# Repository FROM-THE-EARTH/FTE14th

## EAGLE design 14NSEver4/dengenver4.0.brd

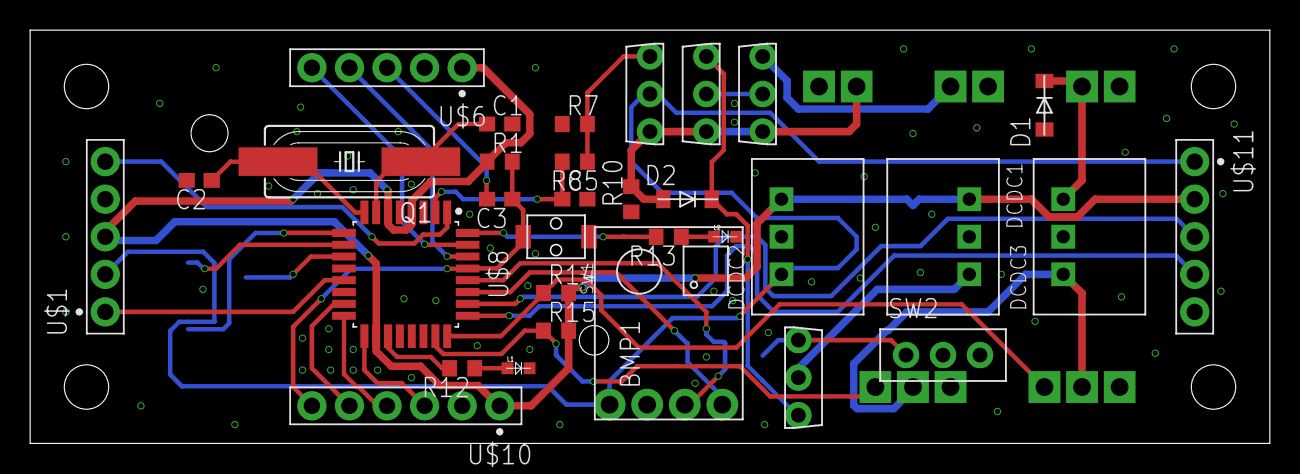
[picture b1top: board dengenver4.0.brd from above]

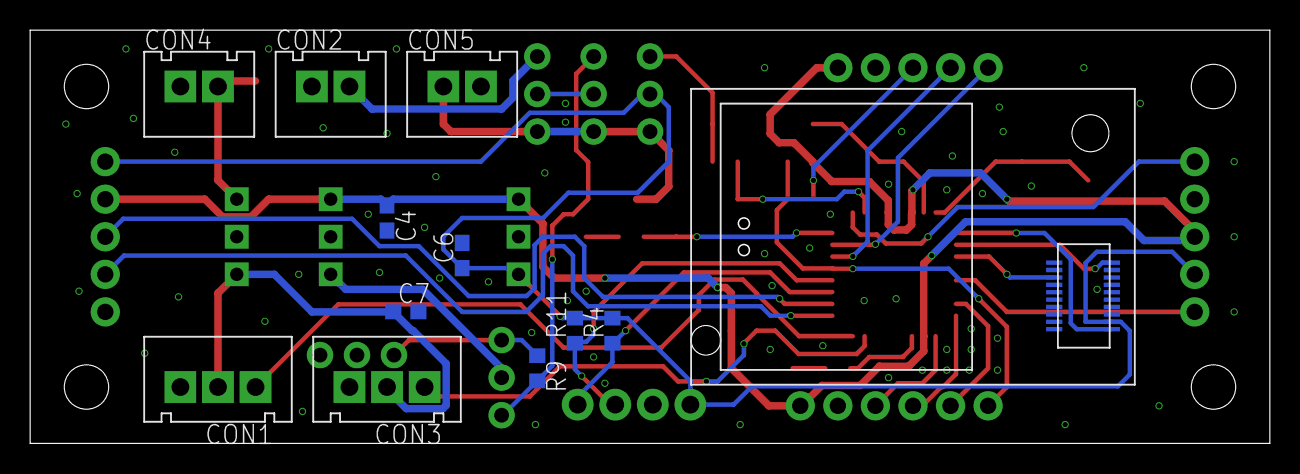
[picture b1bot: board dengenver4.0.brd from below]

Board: 2 copper layers, 83.8 x 27.9 mm, 44 parts (12 on the bottom side), 37 nets.

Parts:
BMP1: BMP180; GY-68
C1, C2: 22p; C1608
C3: 0.1μ; C1608
C4, C6: 3.3uF; C1608
C5: 10uF; C1608
C7: 3.3uF; C0603
CON1, CON3: 3PIN
CON2, CON4, CON5: 2PIN
D1, D2: SOD-123
DCDC1, DCDC3: 5V1A_M78AR05-1
DCDC2: 3.3V1A_M78AR033-1
IM2: IM920_IM920C
L1, L2: OSXX1608C1A
Q1: 16mhz; HC49UP
R1, R4, R7, R11: 10k; R0603
R8, R10: 1k; R0603
R9: 100k; R0603
R12, R13: 100; R0603
R14, R15: 4.7k; R0603
SW1: TVAF06-A020B-R
SW2: SRIDE_SWITCH
U$1, U$6, U$11: 1X5; HDRVR5W64P254_1X5_1310X250X865B
U$2, U$4, U$5: 2SJ681-PCH; 2SJ681
U$3: 2SK4017-NCH; 2SK4017
U$8: ATMEGA328P-AU; QFP80P900X900X120-32N
U$10: 1X61X6_2.5; HDRVR6W64P254_1X6_1564X250X865B

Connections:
+3V3: BMP1.P1, C6.1, DCDC2.VOUT, IM2.$P17, R4.2, R11.2, U$1.2, U$3.DRAIN, U$11.1
+5V: C4.1, DCDC1.VOUT, DCDC2.VIN, R1.1, R14.2, R15.2, U$1.3, U$6.1, U$8.AVCC, U$8.VCC1, U$8.VCC2, U$10.1, U$11.2
+5V1: DCDC1.VIN, U$5.DRAIN
BORD1: U$1.5, U$8.PD3
BORD2: U$1.1, U$8.PB1
BORDRX: U$8.PC3, U$11.3
BORDTX: U$8.PC2, U$11.4
FP: CON5.P$1, D2.C, R10.2, U$2.GATE, U$3.GATE, U$4.GATE
FP_CHECKER: C5.1, R8.2, U$8.PD4
GND: BMP1.P2, C1.2, C2.2, C4.2, C5.2, C6.2, C7.2, CON1.P$3, CON2.P$1, CON3.P$3, CON4.P$1, CON5.P$2, DCDC1.GND, DCDC2.GND, DCDC3.GND, IM2.$P18, L1.CT, L2.CT, R7.1, R10.1, SW1.P$1, SW2.LR, U$1.4, U$6.2, U$8.GND1, U$8.GND2, U$8.GND3, U$10.2, U$11.5
IM_BUSY: IM2.$P1, U$8.PD6
IM_RESET: IM2.$P19, U$8.PD5
LED_1.0: R13.2, U$8.PD2
LED_1.1: R12.2, U$8.ADC6
MISO: U$8.PB4, U$10.4
MOSI: U$8.PB3, U$10.5
unnamed: U$2.DRAIN, U$4.DRAIN
unnamed: D2.A, R9.2, U$4.SOURCE, U$5.SOURCE
unnamed: L2.AN, R13.1
unnamed: L1.AN, R12.1
unnamed: C1.1, Q1.1, U$8.PB6
unnamed: C2.1, Q1.2, U$8.PB7
unnamed: R7.2, R8.1, U$3.SOURCE
RAW: CON2.P$2, U$2.SOURCE
RESET: C3.2, U$6.3
RESETB: C3.1, R1.2, SW1.P$2, U$8.PC6, U$10.6
RX: U$6.4, U$8.PD0
RX_IM: IM2.$P6, U$8.PD7
SCK: U$8.PB5, U$10.3
SCL: BMP1.P3, R11.1, U$8.PC5
SDA: BMP1.P4, R4.1, U$8.PC4
SERVO1: CON1.P$1, R14.1, U$8.PC1
SERVO2: CON3.P$1, R15.1, U$8.PC0
SERVO5V: C7.1, CON1.P$2, CON3.P$2, DCDC3.VOUT
SERVORAW: CON4.P$2, D1.A, DCDC3.VIN
SW: R9.1, SW2.L, U$5.GATE
TX: U$6.5, U$8.PD1

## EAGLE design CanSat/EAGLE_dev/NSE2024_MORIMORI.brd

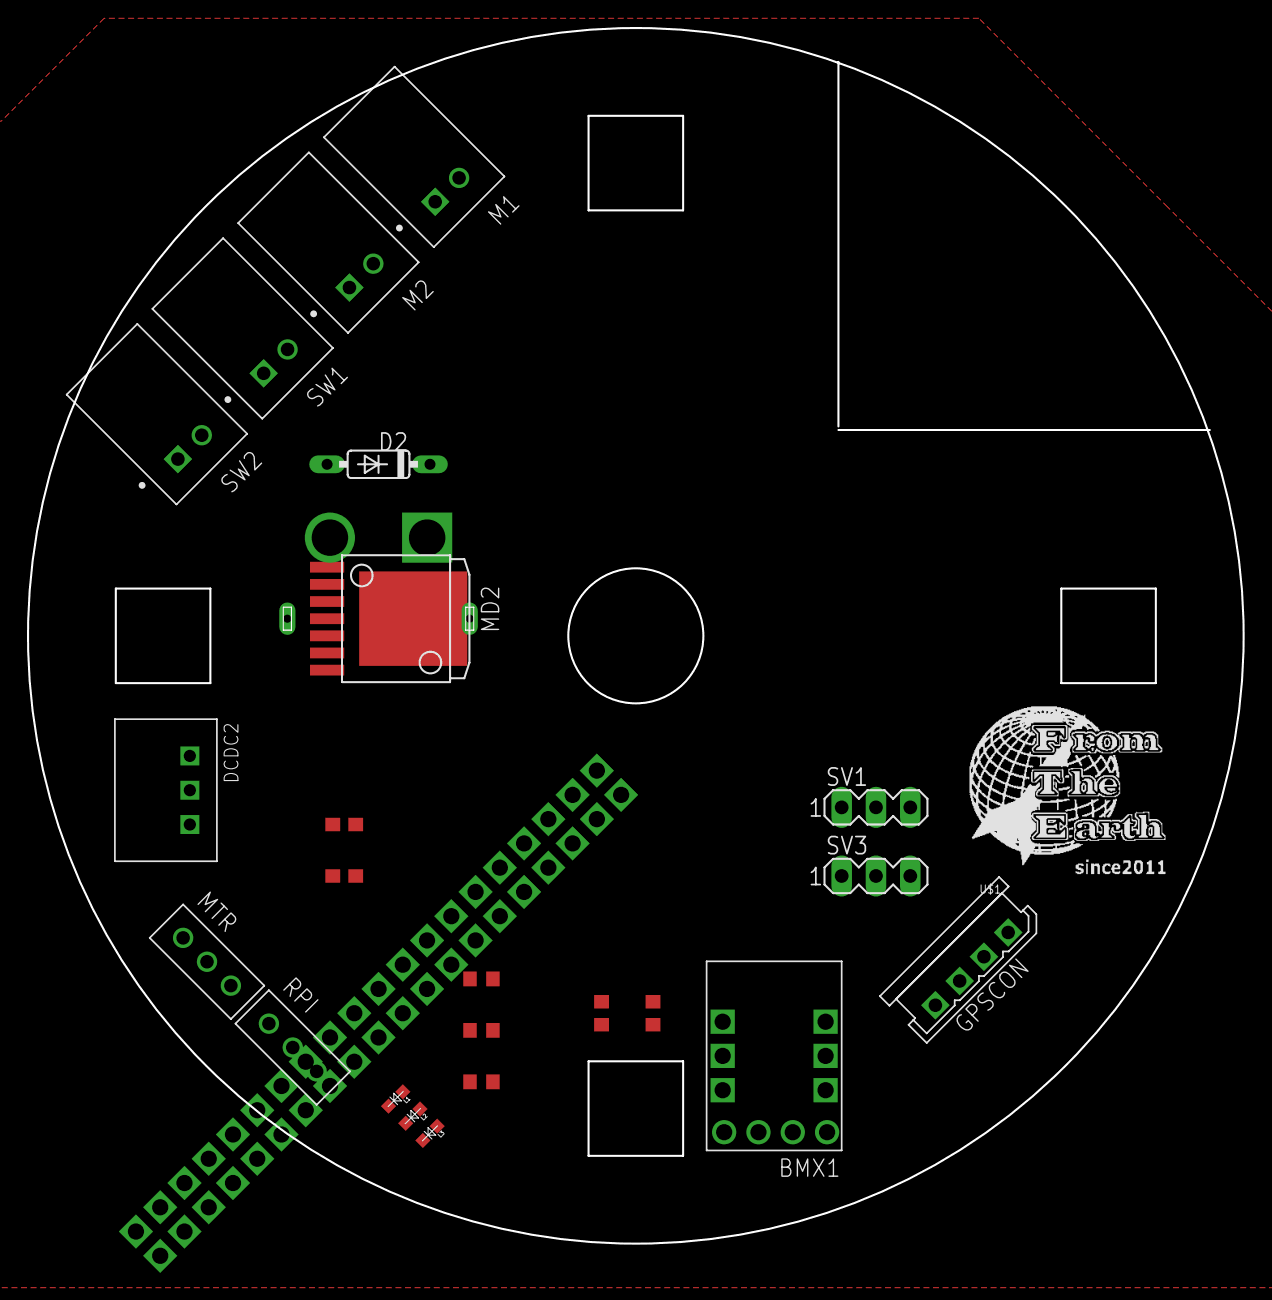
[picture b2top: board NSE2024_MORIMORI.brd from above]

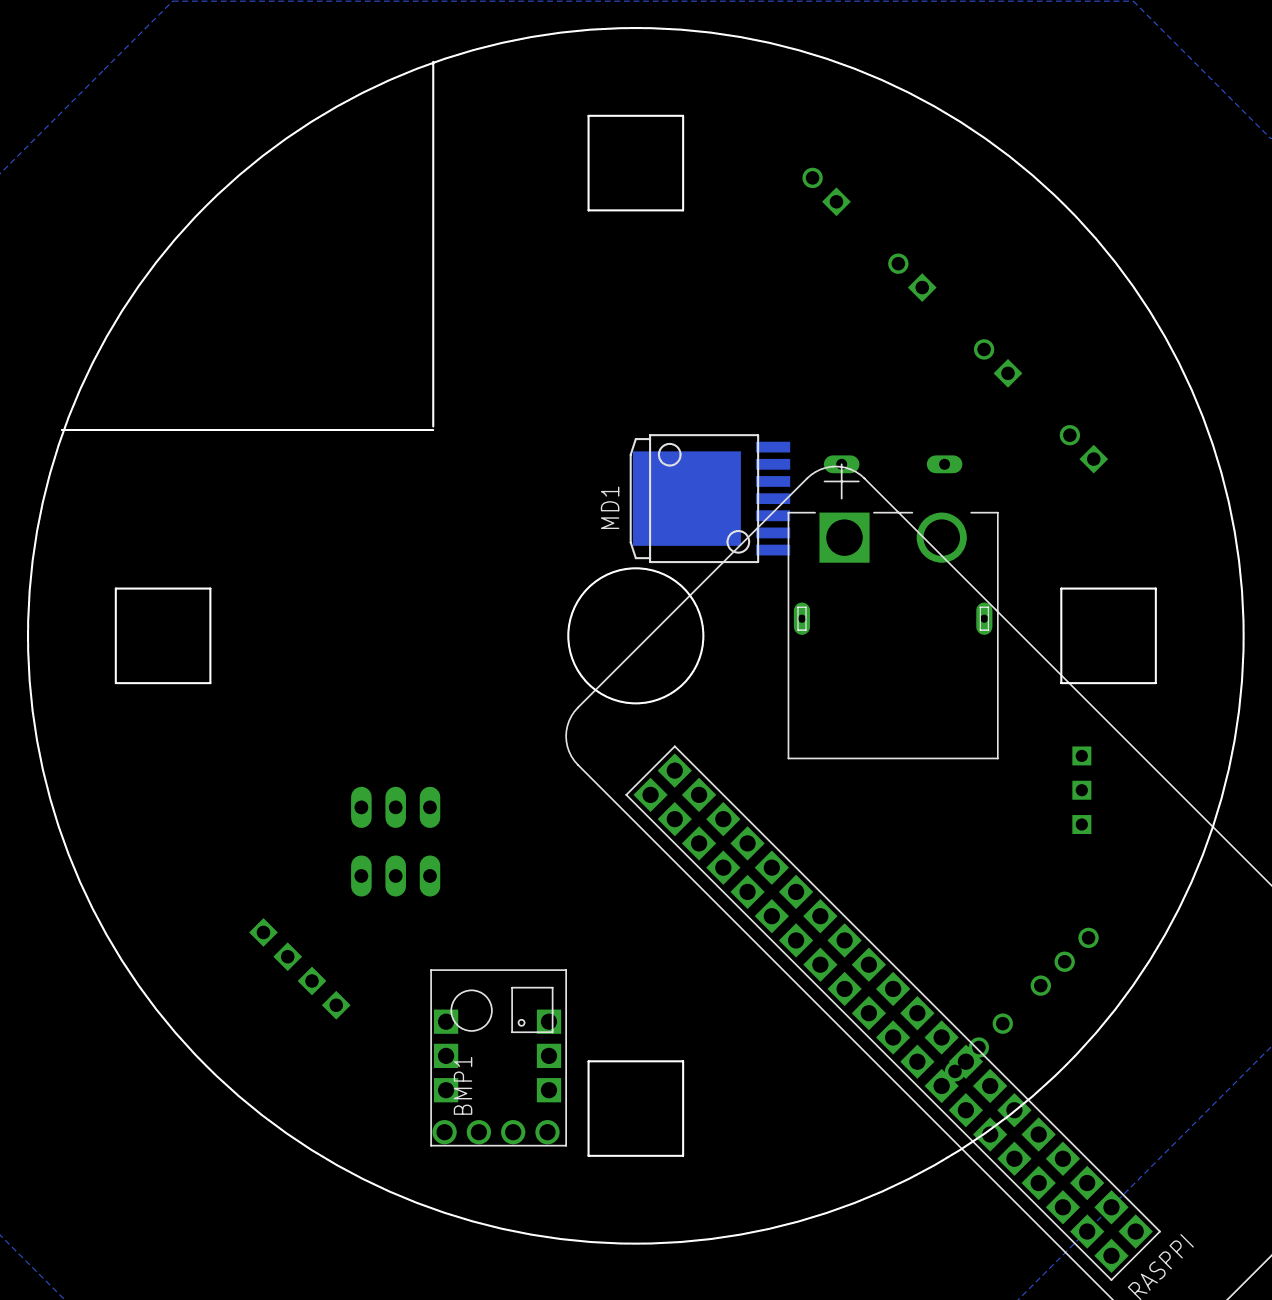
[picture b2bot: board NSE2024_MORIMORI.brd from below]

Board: 2 copper layers, 90.0 x 90.0 mm, 28 parts (4 on the bottom side), 27 nets, no tracks yet.

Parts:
BMP1: BMP180; GY-68
BMX1: BMX055
C1, C3: 10μF; C0603
D2: 1N4148DO35-7; DO35-7
DCDC2: 3.3V1A_M78AR033-1
GPSCON: 2.5_MINI-SPOX_4PIN
L1, L2, L3: OSXX1608C1A
M1, M2: S2B-XH-A(LF)(SN); JST_S2B-XH-A(LF)(SN)
MD1, MD2: BD6222HFP-TR
MTR: SRIDE_SWITCH
POWER: XT60PW-M; AMASS_XT60PW-M
R4, R6: 1k; R0603
R7, R12, R14: 100; R0603
RASPPI: RASPBERYPIZEROW
RPI: SRIDE_SWITCH
SV1, SV3: MA03-1
SW1, SW2: S2B-XH-A(LF)(SN); JST_S2B-XH-A(LF)(SN)
U$1: F.T.E.LOGO; LOGO

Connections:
+3V3: BMP1.P1, BMX1.3V3, BMX1.VCC, BMX1.VCCIO, R4.1, R6.1, RASPPI.3.3V1, RASPPI.3.3V2
+5V: C1.1, DCDC2.VOUT, GPSCON.P$4, RASPPI.5V1, RASPPI.5V2, RPI.L, SV1.2, SV3.2
+12V: C3.1, D2.C, DCDC2.VIN, MD1.VCC, MD1.VREV, MD2.VCC, MD2.VREV, MTR.L
GND: BMP1.P2, BMX1.GND, C1.2, C3.2, DCDC2.GND, GPSCON.P$1, L1.CT, L2.CT, L3.CT, MD1.BGND, MD1.GND, MD2.BGND, MD2.GND, POWER.1, RASPPI.GND1, RASPPI.GND2, RASPPI.GND3, RASPPI.GND4, RASPPI.GND5, RASPPI.GND6, RASPPI.GND7, RASPPI.GND8, SV1.1, SV3.1, SW1.2, SW2.1
GPS_RX: GPSCON.P$2, RASPPI.GPIO15
GPS_TX: GPSCON.P$3, RASPPI.GPIO14
LED0: R12.1, RASPPI.GPIO25
LED1: R7.1, RASPPI.GPIO8
LED2: R14.1, RASPPI.GPIO7
MD1_F: MD1.FIN, RASPPI.GPIO5
MD1_O1: M1.1, MD1.OUT1
MD1_O2: M1.2, MD1.OUT2
MD1_R: MD1.RIN, RASPPI.GPIO6
MD2_F: MD2.FIN, RASPPI.GPIO13
MD2_O1: M2.2, MD2.OUT1
MD2_O2: M2.1, MD2.OUT2
MD2_R: MD2.RIN, RASPPI.GPIO19
unnamed: D2.A, POWER.2
unnamed: L1.AN, R12.2
unnamed: L2.AN, R7.2
unnamed: L3.AN, R14.2
PWM: RASPPI.GPIO10, SV3.3
PWM1: RASPPI.GPIO9, SV1.3
SCL: BMP1.P3, BMX1.SCL, R4.2, RASPPI.GPIO3
SDA: BMP1.P4, BMX1.SDA, R6.2, RASPPI.GPIO2
SW1: RASPPI.GPIO16, SW1.1
SW2: RASPPI.GPIO20, SW2.2

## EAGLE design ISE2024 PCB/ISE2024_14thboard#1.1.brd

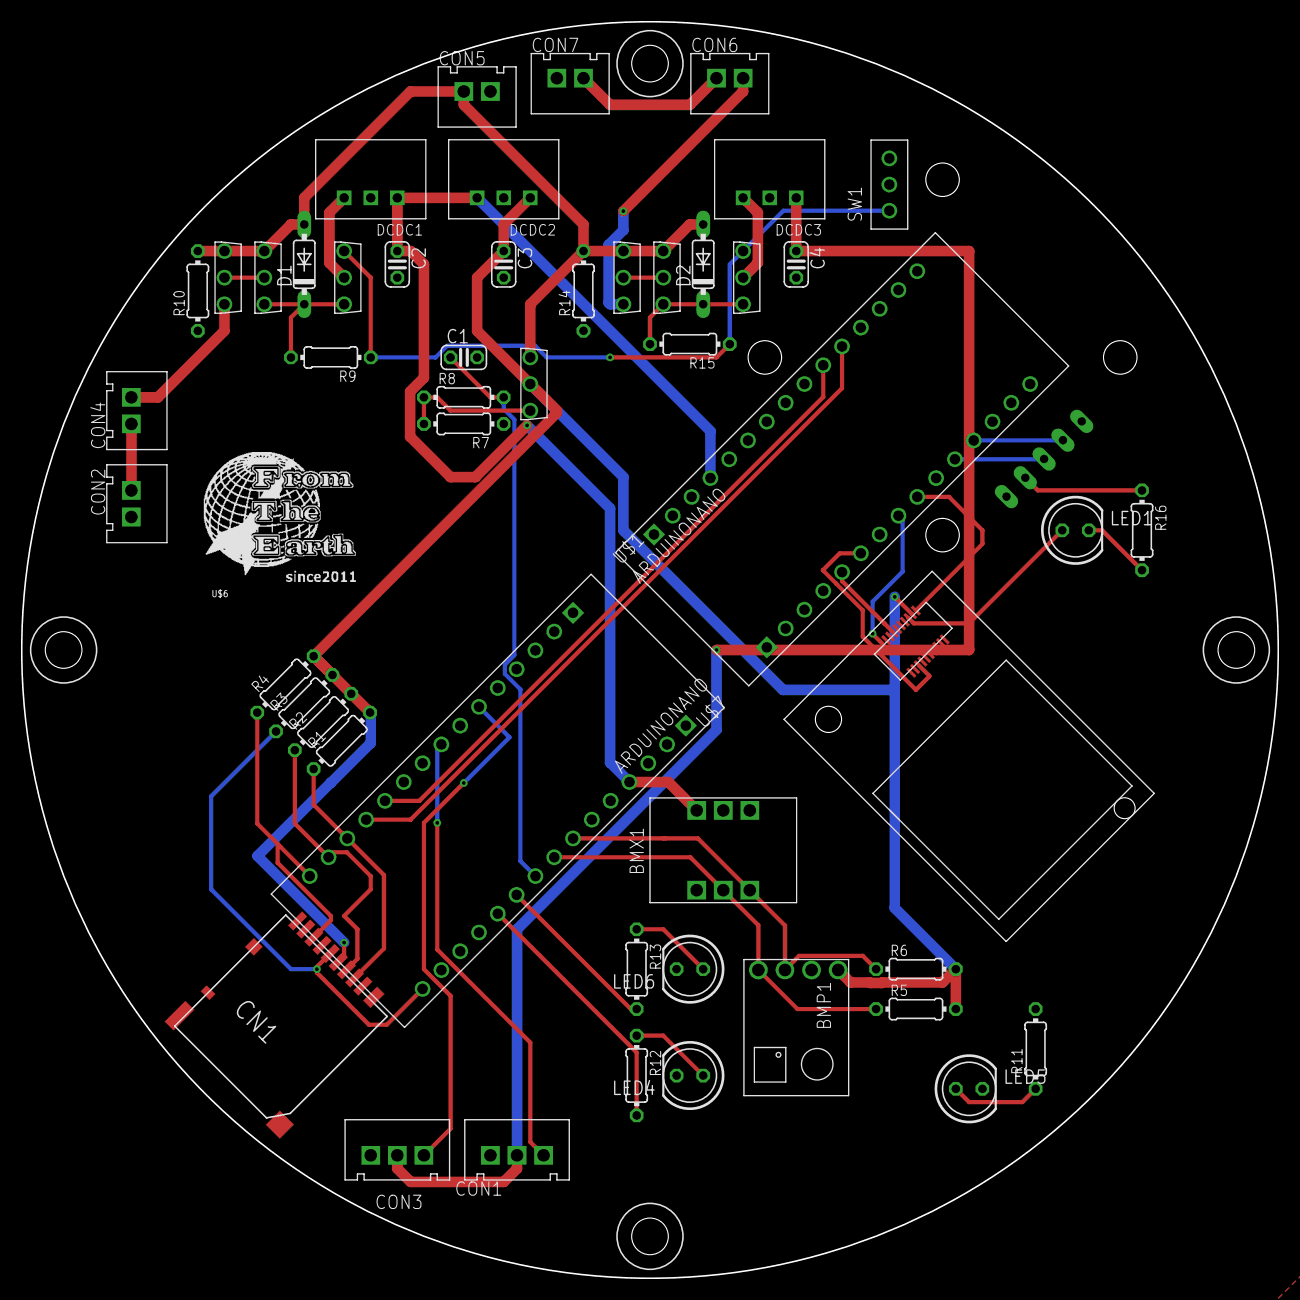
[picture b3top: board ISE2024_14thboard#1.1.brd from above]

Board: 2 copper layers, 120.0 x 120.0 mm, 52 parts (1 on the bottom side), 41 nets.

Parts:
BMP1: BMP180; GY-68
BMX1: BMX055
C1: 10uF; C025-024X044
C2, C3, C4: 3.3uF; C025-024X044
CN1: DM3AT
CON1, CON3: 3PIN
CON2, CON4, CON5, CON6, CON7: 2PIN
D1, D2: 1N4148DO35-7; DO35-7
DCDC1, DCDC3: 5V1A_M78AR05-1
DCDC2: 3.3V1A_M78AR033-1
IM2: IM920_IM920C
LED1, LED4, LED5, LED6: LED5MM
R1, R2, R3, R4, R5, R6, R7: 10k; 0204/7
R8, R10, R14: 1k; 0204/7
R9, R15: 100k; 0204/7
R11, R12, R13, R16: 100; 0204/7
SW1: SRIDE_SWITCH
U$1, U$7: ARDUINONANO
U$2, U$4, U$5, U$8, U$9, U$10: 2SJ681-PCH; 2SJ681
U$3: 2SK4017-NCH; 2SK4017
U$6: F.T.E.LOGO; LOGO
U$11: AE-GYSFDMAXB

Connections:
3.3_RAW1: CON4.P$2, U$2.SOURCE
3.3_RAW2: CON2.P$2, CON4.P$1
3.3_SV1: CON6.P$2, U$8.SOURCE
3.3_SV2: CON6.P$1, CON7.P$2
+3V3: BMP1.P1, C3.1, CN1.VDD, DCDC2.VOUT, IM2.$P17, R1.2, R2.2, R3.2, R4.2, R5.2, R6.2, U$3.DRAIN
+5V: BMX1.VCC, C2.1, DCDC1.VOUT, DCDC2.VIN, U$1.5V, U$7.5V
+5V1: DCDC1.VIN, U$5.DRAIN
+5V2: DCDC3.VIN, U$9.DRAIN
+5V_SV: C4.1, CON1.P$2, CON3.P$2, DCDC3.VOUT
BOARD-RX: U$1.D8, U$7.D16
BOARD-TX: U$1.D9, U$7.D15
CLK: CN1.CLK, R3.1, U$1.D13
FP: CON5.P$1, D1.A, D2.A, R10.2, R14.2, U$2.GATE, U$3.GATE, U$4.GATE, U$8.GATE, U$10.GATE
FP_CHECKER: C1.1, R8.2, U$1.D17
GND: BMP1.P2, BMX1.GND, C1.2, C2.2, C3.2, C4.2, CN1.VSS, CON1.P$3, CON2.P$1, CON3.P$3, CON5.P$2, CON7.P$1, DCDC1.GND, DCDC2.GND, DCDC3.GND, IM2.$P18, LED4.K, LED5.K, LED6.K, R7.1, R10.1, R14.1, R16.1, SW1.LR, U$1.GND1, U$1.GND2, U$7.GND1, U$11.P2
IM_BUSY: IM2.$P1, U$7.D5
IM_RESET: IM2.$P19, U$7.D6
LED: IM2.$P15, LED1.A
LED1.0: R13.2, U$1.D16
LED1.1: R12.2, U$1.D15
unnamed: U$2.DRAIN, U$4.DRAIN
unnamed: LED6.A, R13.1
unnamed: D1.C, R9.2, U$4.SOURCE, U$5.SOURCE
unnamed: D2.C, R15.2, U$9.SOURCE, U$10.SOURCE
unnamed: U$8.DRAIN, U$10.DRAIN
unnamed: LED4.A, R12.1
unnamed: LED1.K, R16.2
unnamed: LED5.A, R11.1
unnamed: R7.2, R8.1, U$3.SOURCE
RX_GPS: U$7.D9, U$11.P4
RX_IM: IM2.$P6, U$7.D3
SCL: BMP1.P3, BMX1.SCL, R6.1, U$1.D19
SD-MISO: CN1.DAT0, R4.1, U$1.D12
SD-MOSI: CN1.CMD, R2.1, U$1.D11
SD-SS: CN1.CD/DAT3, R1.1, U$1.D10
SDA: BMP1.P4, BMX1.SDA, R5.1, U$1.D18
SERVO1: CON1.P$1, U$1.D5
SERVO2: CON3.P$1, U$1.D3
SW: R9.1, R15.1, SW1.L, U$5.GATE, U$9.GATE
TX_GPS: U$7.D8, U$11.P3
TX_IM: IM2.$P7, U$7.D2

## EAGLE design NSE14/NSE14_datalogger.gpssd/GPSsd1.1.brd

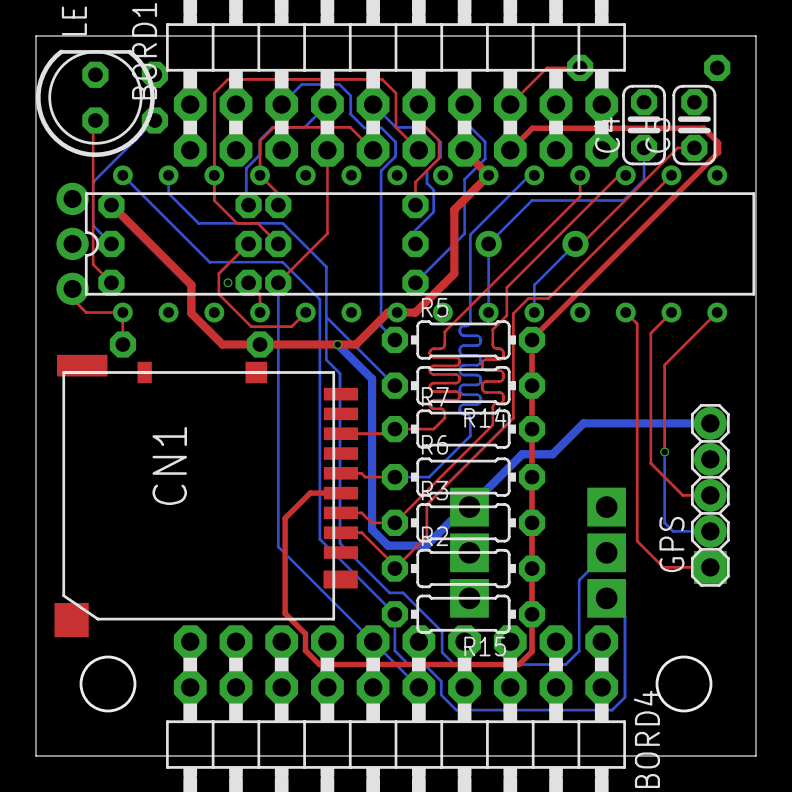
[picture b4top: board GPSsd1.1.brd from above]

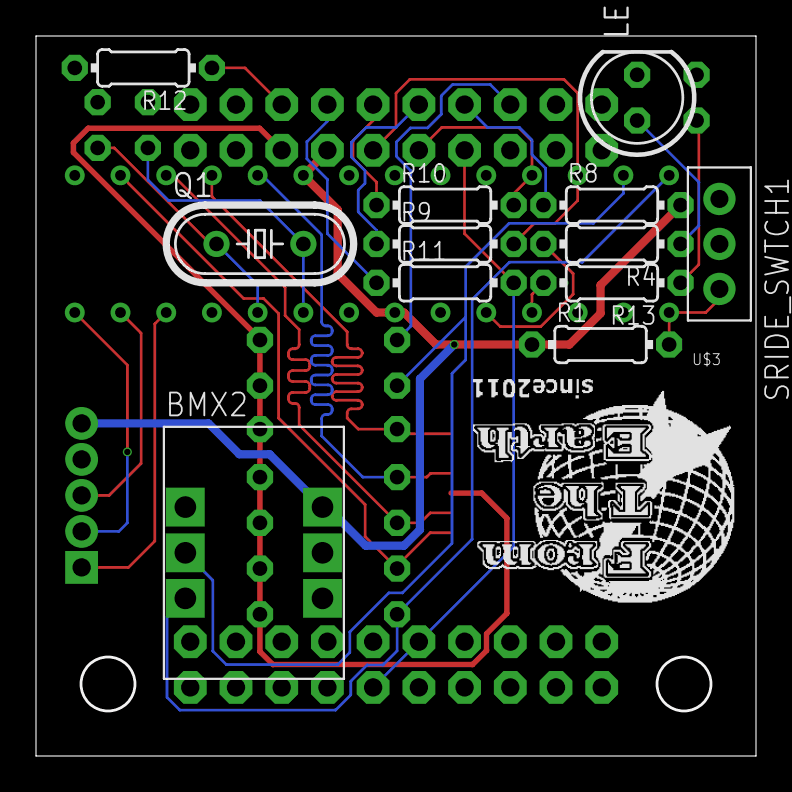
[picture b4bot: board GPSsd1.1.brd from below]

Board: 2 copper layers, 40.0 x 40.0 mm, 28 parts (13 on the bottom side), 28 nets.

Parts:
BMX2: BMX055
BORD1, BORD4: 2X10/90
C4, C5: 22p; C025-024X044
CN1: DM3AT
GPS: 1_05X2MM
LED4, LED6: LED5MM
Q1: 16mhz; HC49/S
R1, R5, R8, R9, R10, R11, R12: 0204/7
R2, R3, R6, R7, R14, R15: 10k; 0204/7
R4, R13: 100; 0204/7
SRIDE_SWTCH1: SRIDE_SWITCH
U$1: ATMEGA238P; ATMEGA328P
U$3: F.T.E.LOGO; LOGO

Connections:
+3V3: BORD1.15, CN1.VDD, R2.2, R3.2, R5.2, R6.2, R7.2, R14.1, R15.1
+5V: BMX2.VCC, BORD1.13, GPS.5, R1.1, R8.2, U$1.AVCC, U$1.VCC
BORDRX: BORD1.11, R9.2, U$1.D17
BORDTX: BORD1.9, R10.2, U$1.D16
CLK: CN1.CLK, R6.1, U$1.SCKD13
GND: BMX2.GND, BORD1.5, C4.2, C5.2, CN1.VSS, GPS.4, LED4.K, LED6.K, R12.2, SRIDE_SWTCH1.LR, U$1.GND1, U$1.GND2
GPSRX: GPS.3, U$1.D7
GPSTX: GPS.2, U$1.D8
LED1.0: R13.2, U$1.D2
LED1.1: R4.2, U$1.D3
unnamed: LED6.A, R13.1
unnamed: BORD1.6, R5.1
unnamed: BORD1.8, R8.1
unnamed: BORD1.10, R9.1
unnamed: C5.1, Q1.1, U$1.PB7
unnamed: R1.2, SRIDE_SWTCH1.R, U$1.RESET
unnamed: C4.1, Q1.2, U$1.PB6
unnamed: BORD1.12, R10.1
unnamed: BORD1.14, R11.1
unnamed: BORD1.16, R12.1
unnamed: LED4.A, R4.1
RST: GPS.1, U$1.D6
SCL: BMX2.SCL, R15.2, U$1.SCLD19
SD-MISO: CN1.DAT0, R7.1, U$1.MISOD12
SD-MOSI: CN1.CMD, R3.1, U$1.MOSID11
SD-SS: CN1.CD/DAT3, R2.1, U$1.SSD10
SDA: BMX2.SDA, R14.2, U$1.SDAD18
SERVO: BORD1.7, BORD4.10, BORD4.11, R11.2

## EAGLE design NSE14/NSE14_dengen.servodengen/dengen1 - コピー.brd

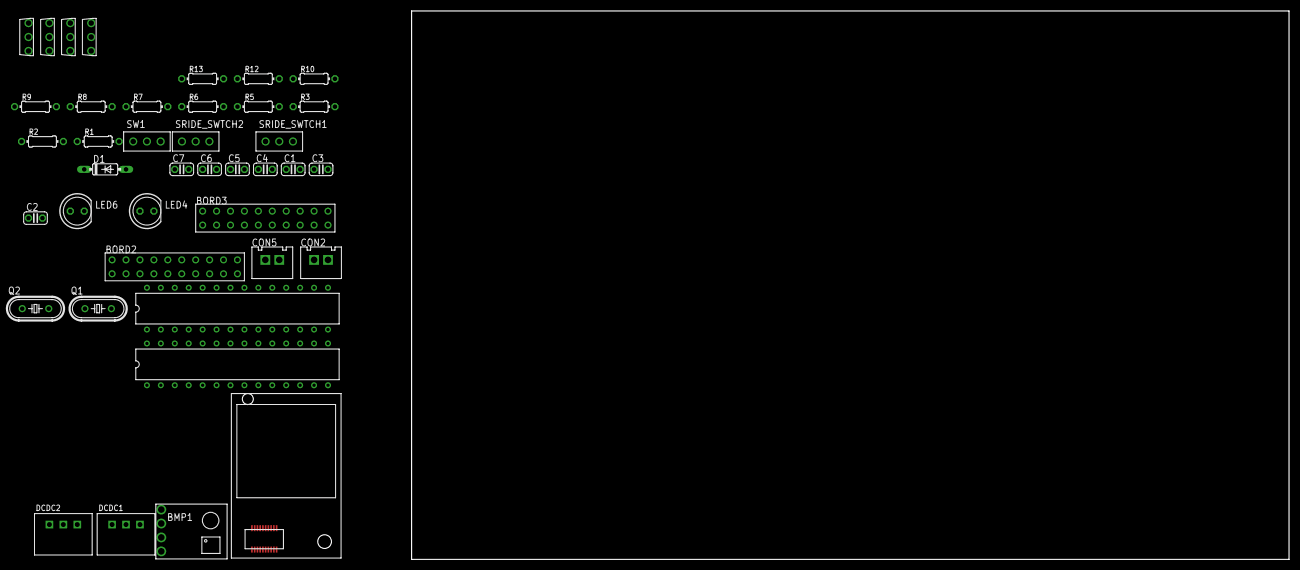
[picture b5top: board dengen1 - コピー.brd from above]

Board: 2 copper layers, 160.0 x 100.0 mm, 40 parts (0 on the bottom side), 30 nets, no tracks yet.

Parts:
BMP1: BMP180; GY-68
BORD2, BORD3: 2X10
C1: 10uF; C025-024X044
C2, C3: 3.3uF; C025-024X044
C4, C5, C6, C7: 22p; C025-024X044
CON2, CON5: 2PIN
D1: 1N4148DO35-7; DO35-7
DCDC1: 5V1A_M78AR05-1
DCDC2: 3.3V1A_M78AR033-1
IM2: IM920_IM920C
LED4, LED6: LED5MM
Q1, Q2: 16mhz; HC49/S
R1, R2, R3: 0204/7
R5, R6, R7: 10k; 0204/7
R8, R10: 1k; 0204/7
R9: 100k; 0204/7
R12, R13: 100; 0204/7
SRIDE_SWTCH1, SRIDE_SWTCH2: SRIDE_SWITCH
SW1: SRIDE_SWITCH
U$1, U$6: ATMEGA238P; ATMEGA328P
U$2, U$4, U$5: 2SJ681-PCH; 2SJ681
U$3: 2SK4017-NCH; 2SK4017

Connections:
+3V3: BMP1.P1, BORD2.P$9, BORD2.P$10, BORD3.P$6, BORD3.P$15, C3.1, DCDC2.VOUT, IM2.$P17, R3.2, R5.2, R6.2, U$3.DRAIN
+5V: BORD2.P$11, BORD2.P$12, BORD3.P$8, BORD3.P$13, C2.1, DCDC1.VOUT, DCDC2.VIN, R1.1, R2.1, U$1.AVCC, U$1.VCC, U$6.AVCC, U$6.VCC
+5V1: DCDC1.VIN, U$5.DRAIN
BORDRX: BORD3.P$10, BORD3.P$11, U$6.D17
BORDTX: BORD3.P$9, BORD3.P$12, U$6.D16
FP: CON5.P$1, D1.A, R10.2, U$2.GATE, U$3.GATE, U$4.GATE
FP_CHECKER: C1.1, R8.2
GND: BMP1.P2, BORD2.P$8, BORD2.P$13, BORD3.P$5, BORD3.P$16, C1.2, C2.2, C3.2, C4.2, C5.2, C6.2, C7.2, CON2.P$1, CON5.P$2, DCDC1.GND, DCDC2.GND, IM2.$P18, LED4.K, LED6.K, R7.1, R10.1, SRIDE_SWTCH1.LR, SRIDE_SWTCH2.LR, SW1.LR, U$1.GND1, U$1.GND2, U$6.GND1, U$6.GND2
IM_BUSY: IM2.$P1, U$6.D6
IM_RESET: IM2.$P19, U$6.D5
LED1.0: R13.2, U$6.D2
LED1.1: R12.2, U$6.D3
unnamed: U$2.DRAIN, U$4.DRAIN
unnamed: C6.1, Q2.2, U$6.PB6
unnamed: D1.C, R9.2, U$4.SOURCE, U$5.SOURCE
unnamed: C7.1, Q2.1, U$6.PB7
unnamed: C5.1, Q1.1, U$1.PB7
unnamed: R1.2, SRIDE_SWTCH1.R, U$1.RESET
unnamed: C4.1, Q1.2, U$1.PB6
unnamed: R2.2, SRIDE_SWTCH2.R, U$6.RESET
unnamed: LED6.A, R13.1
unnamed: LED4.A, R12.1
unnamed: R7.2, R8.1, U$3.SOURCE
RAW: CON2.P$2, U$2.SOURCE
RX_IM: IM2.$P6, U$6.D7
SCL: BMP1.P3, R6.1, U$6.SCLD19
SDA: BMP1.P4, R5.1, U$6.SDAD18
SERVO: BORD3.P$7, BORD3.P$14, R3.1, U$6.D15
SW: R9.1, SW1.L, U$5.GATE
TX_IM: IM2.$P7, U$6.D8
